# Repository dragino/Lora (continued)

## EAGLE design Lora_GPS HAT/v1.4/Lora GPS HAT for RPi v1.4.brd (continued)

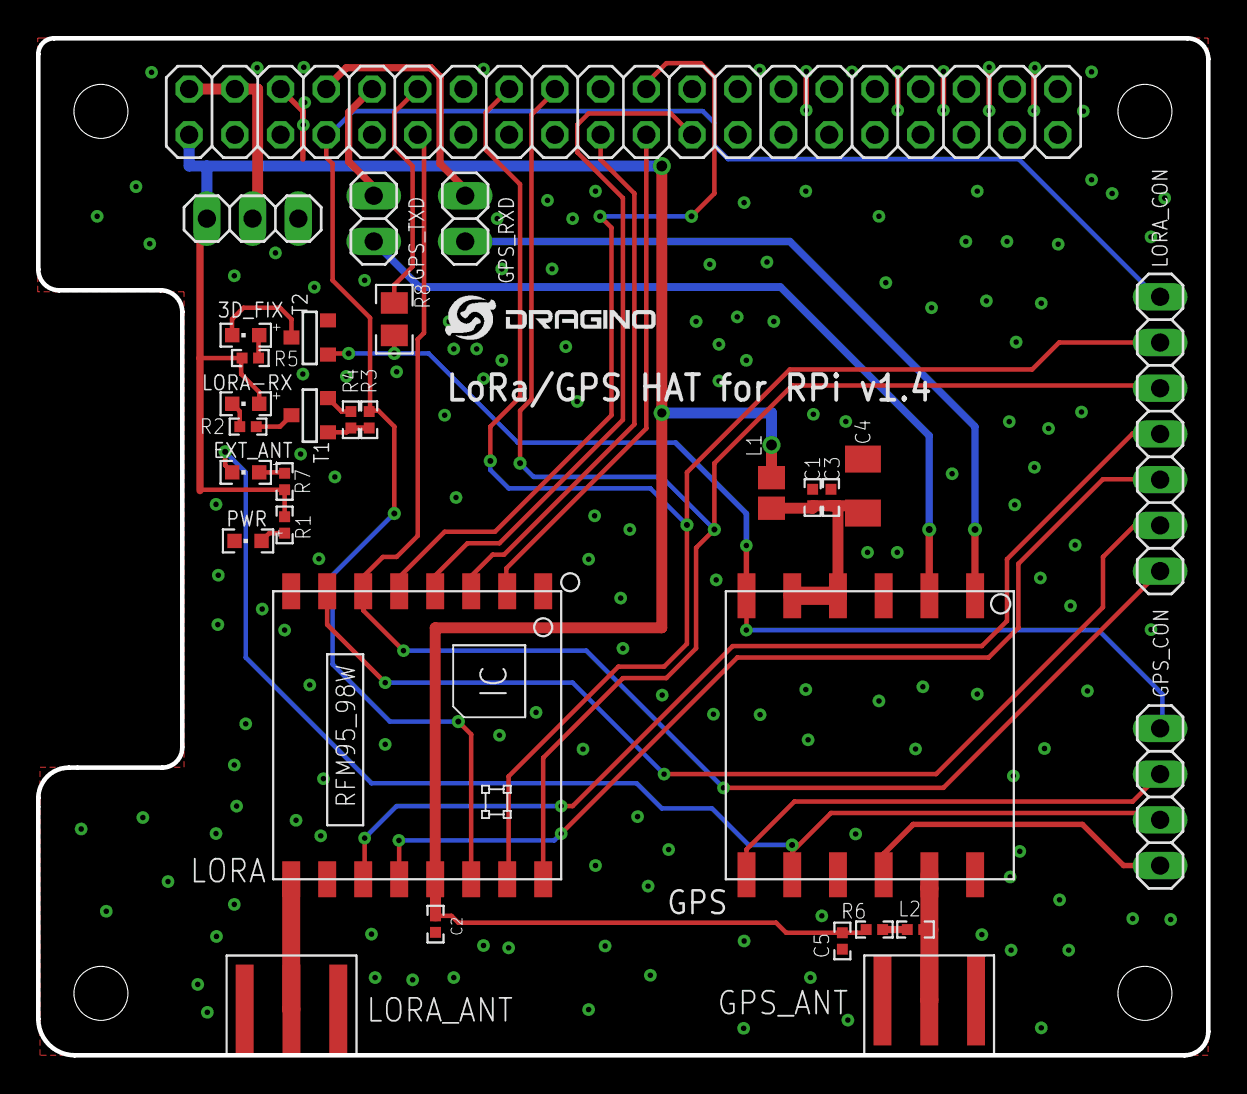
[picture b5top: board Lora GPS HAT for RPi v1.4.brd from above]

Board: 2 copper layers, 65.0 x 56.5 mm, 32 parts (0 on the bottom side), 34 nets.
